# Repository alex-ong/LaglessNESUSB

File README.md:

What is this?
===
This repository contains two main parts - a hardware folder which includes all the parts required to
make a two player adapter enclosure, and a software folder, arduino code required to create
a lagless adapter.

Why is this lagless?
===
The software leverages [MHeironimus's Joystick2](https://github.com/MHeironimus/ArduinoJoystickLibrary/tree/version-1.0/Joystick2) library, which creates a 1000hz usb device.
It is a simplified version of [mcgurk](https://github.com/mcgurk/Arduino-USB-HID-RetroJoystickAdapter)'s more universal adapter that polls as quickly as possible (10000hz+)
Total input delay is <1000hz. Pressing two keys at almost the same time will report button presses
2-3 milliseconds apart, in the correct order. This is more accurate than lower usb polling combos,
where pressing two buttons close together will wrap them as sent simultaneously.

 * [Hardware](https://github.com/alex-ong/LaglessNESUSB/tree/master/Hardware/NO_PCB)

 * [Software](https://github.com/alex-ong/LaglessNESUSB/tree/master/Software)

Basic instructions
===
 1. Build hardware via laser cutting / screwing, soldering
 2. Flash software from software folder.
 3. Plug in, enjoy!

Future feature list
===

A single button will toggle between nodes, with two LEDs (one for mode, one for output).
Modes could include
 * Flashing an LED when key-down is detected. Use this in combination with a high speed camera to calculate input delay.
 * Auto-fire of arrow keys at 30hz, after a short delay
 * Adding delay to input to do A/B testing on users to detect minimum delay threshold.
 
Testing polling rate / minimum time between keymessages
===
You can use [this tool](https://github.com/alex-ong/UnityInputDelayTester/releases) to ensure that polling rate is 1ms. You can compare with other usb adapters, and your keyboard.
The idea is to strum two keys as close together as possible, without being simultaneous. It will figure out
the minimum time between key messages. Note that some keyboards are advertised as 1000hz, but wrap key events into 5ms polling rates.
This means if you press two keys 1ms apart, they are reported in the same 5ms block with the same timestamp.

Bill of Materials
===
| Electronics                | Cost  | Link                                             |
|----------------------------|-------|--------------------------------------------------|
| Arduino pro micro 5v 16mhz | $3.00 | [link](https://www.aliexpress.com/item/1348800135.html)  |
| Female Nes port            | $2.60 x 2 | [link](https://www.aliexpress.com/i/32827585164.html)    |
| Cabling (Ethernet)         | $0.00 |                                                  |
| Micro usb cable            | $1.00 | [link](https://www.aliexpress.com/item/32996600477.html) |

| Enclosure         | Cost | Link                                             |
|-------------------|------|--------------------------------------------------|
| Laser cut plywood | $3.0 | Todo: upload files as 1.5mm and 3mm              |
| Screws            | $2.0 | Todo                                             |
| Standoffs         | $2.0 | Todo                                             |
| Microusb port     | $1.5 | [link](https://www.aliexpress.com/item/32840345016.html) |

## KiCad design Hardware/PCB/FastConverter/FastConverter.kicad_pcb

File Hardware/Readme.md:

NO_PCB - simple construction out of laser cutting and screws etc.
PCB - less simple construction requiring gerber files

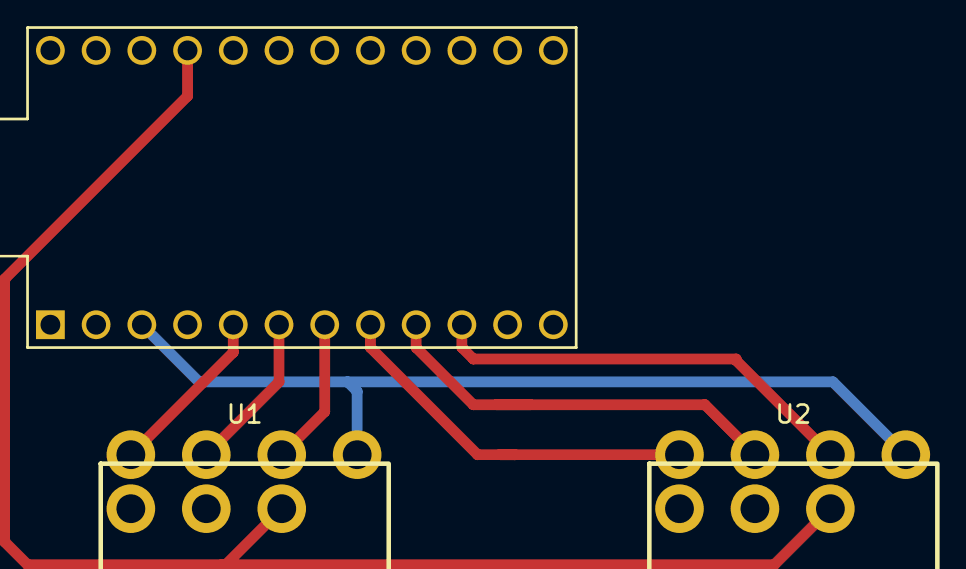
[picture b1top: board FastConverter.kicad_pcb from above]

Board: 2 copper layers, 3 parts (0 on the bottom side), 8 nets.

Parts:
U1, U2: 90DegreePort; NEScontrollerport
U3: ProMicro

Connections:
unnamed: U1.C (Clock), U3.7 (D4)
unnamed: U1.D (Data), U3.5 (SDA)
unnamed: U1.L (Latch), U3.6 (SCL)
unnamed: U1.5V, U2.5V, U3.21 (VCC)
unnamed: U2.C (Clock), U3.10 (E6)
unnamed: U2.D (Data), U3.8 (C6)
unnamed: U1.G (Ground), U2.G (Ground), U3.3 (GND)
unnamed: U2.L (Latch), U3.9 (D7)

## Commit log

2018-11-03 Added software/hardware files. A full build is possible albiet instructions are still to come.
2018-11-03 Added Joystick2 library.
2018-11-03 Updated images.
2018-11-03 Credits at top.
2018-11-03 Italics in previous commit
2018-11-03 Newline changes.
2018-11-03 Updated main page.
2018-11-03 Added bullet points to hardware/software
2018-11-03 Added pictures in hardware folder
2018-11-03 More words / formatting.
2018-11-03 Added hero image.
2018-11-05 Finished instructions for Hardware readme.md
2020-05-17 Add BoM to readme.md
2022-09-23 new: Start working on KiCad6 pcb
2022-09-23 new: hook up PCB
2022-09-23 new: Modify code to support the PCB
2022-09-23 Add circles to edge of board
2022-09-23 Update image
